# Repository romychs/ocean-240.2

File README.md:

# Компьютер "Океан-240.2"

Схема и печатная плата новодела компьютера "Океан-240.2". Разработана на основе информации из журнала МПСС и на основе схем, чертежей, правок пользователей форума zx-pk.ru (__L Juriy__, __tnt23__, __ivagor__ и других).

## Основные характеристики

|-|-|
|----------------------------------------|------------------------|
|Разрядность, бит                        |                      8 |
|Быстродействие (рег. — рег.), операций/с|                600 000 |
|Емкость ОЗУ, К байт					 |                128/512 |
|Емкость РПЗУ, К байт					 |                     16 |
|__Монитор (серийный цветной):__         |                        |
| в монохромном режиме                   |20 строк по 64 символа  |
| в цветном режиме (4 цвета)             |графическое поле 256x256|
|Клавиатура        | алфавитно-цифровая с контроллером на КМОП ИС |        
|__Интерфейс:__                          |                        |
| последовательный                       | RS232                  | 
| три параллельных программируемых канала| КР580ВВ55              |
| интерфейс печатающего устройства       | ИРПР                   |

__Программное обеспечение:__ монитор с графическими функциями, интерпретатор Бэйсик, квазидисковая операционная система, совместимая с CP/M.

Автор ПЭВМ - __Д. А. Тилинин__

[Исходники](Sources)

[Готовые схемы](Export)

[Прошивки для микросхем ПЗУ](ROMs)

[Файлы для производства печатной платы](Gerbers/Gerber_Ocean-240.2_v1.0.3.zip)

[Темы на форуме zx.pk.ru](https://zx-pk.ru/forums/113-okean-240.html)

## Изменения
- В версии v1.0.1, Дизассемблированы обе микросхемы ПЗУ, на основе информации из полученных исходников, немного скорректирована схема и печатная плата.
- В версии v1.0.2, Микросхемы DD5 и DD22 на схемах и шелке KiCAD, ошибочно отмечены как ЛИ1. Ошибку заметил при сборке *felix*.
- В версии v1.0.3, Исправлены ошибки предыдущей версии. Документация в папке Export и герберы сгенерированы в KiCAD. Версия EasyEDA больше не будет дорабатываться.

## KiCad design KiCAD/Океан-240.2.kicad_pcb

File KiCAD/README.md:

# Океан-240.2 Персональный компьютер

Схема и печатная плата в [KiCAD](https://www.kicad.org/) v9.0

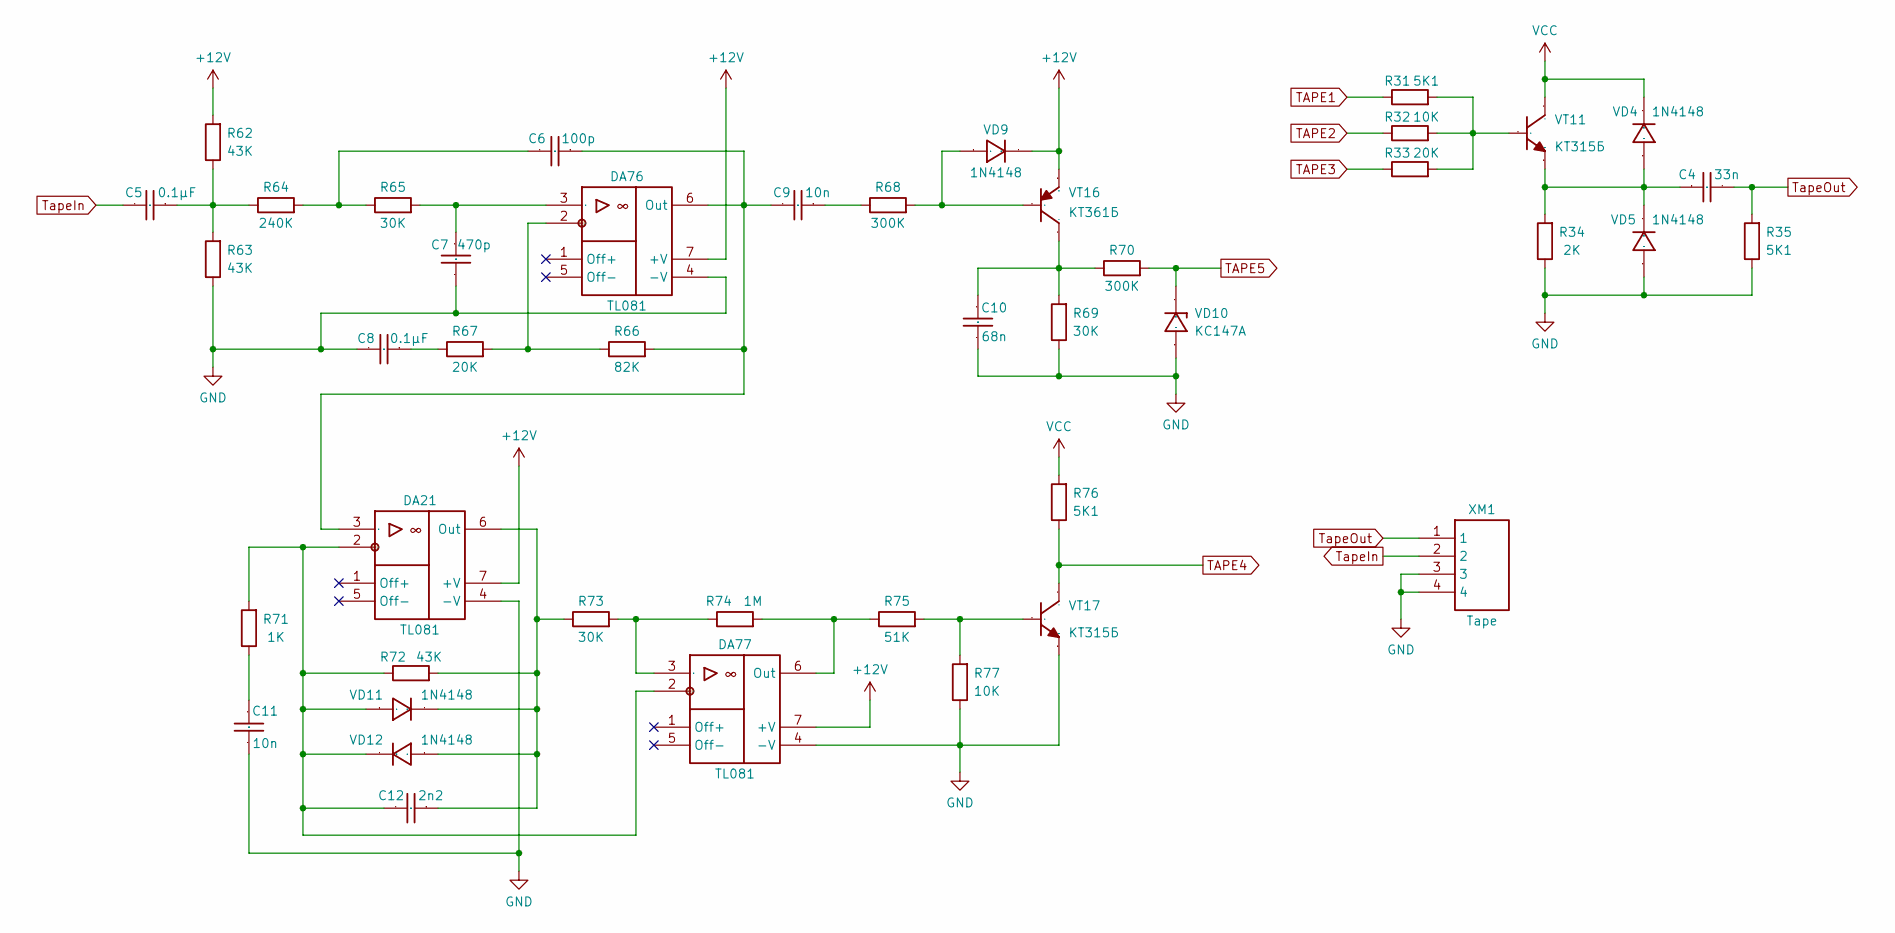
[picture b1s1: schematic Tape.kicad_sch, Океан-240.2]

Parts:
C4: 33n; CAP-TH_L5.08
C5, C8: 0.1μF; CAP-TH_L7.62
C6: 100p; CAP-TH_L7.62
C7: 470p; CAP-TH_L7.62
C9, C11: 10n; CAP-TH_L7.62
C10: 68n; CAP-TH_L7.62
C12: 2n2; CAP-TH_L7.62
DA21, DA76, DA77: TL081; DIP-8_W7.62mm
R31, R35, R76: 5K1; RES_0.125W_P7.62
R32, R77: 10K; RES_0.125W_P7.62
R33, R67: 20K; RES_0.125W_P7.62
R34: 2K; RES_0.125W_P7.62
R62, R63, R72: 43K; RES_0.125W_P7.62
R64: 240K; RES_0.125W_P7.62
R65, R69, R73: 30K; RES_0.125W_P7.62
R66: 82K; RES_0.125W_P7.62
R68, R70: 300K; RES_0.125W_P7.62
R71: 1K; RES_0.125W_P7.62
R74: 1M; RES_0.125W_P7.62
R75: 51K; RES_0.125W_P7.62
VD4, VD5, VD9, VD11, VD12: 1N4148; DO-35_TH_P7.62
VD10: КС147А; DIODE_TH_7.62
VT11, VT17: КТ315Б; KT315_STD
VT16: КТ361Б; KT315_STD
XM1: Tape; HDR-4P-M-P2.54

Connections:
+12V: DA21.7 (+V), DA76.7 (+V), DA77.7 (+V), R62.2, VD9.2 (K), VT16.1 (E); also elsewhere on the board
GND: C7.1, C8.2, C10.1, C11.1, DA21.4 (-V), DA76.4 (-V), DA77.4 (-V), R34.1, R35.1, R63.1, R69.1, R77.1, VD5.1 (A), VD10.1 (A), VT17.1 (E), XM1.3, XM1.4; also elsewhere on the board
unnamed: C5.1, R62.1, R63.2, R64.1
unnamed: C6.2, R64.2, R65.1
unnamed: C8.1, R67.1
unnamed: C9.1, R68.1
unnamed: C11.2, R71.1
unnamed: C6.1, C9.2, DA21.3 (+), DA76.6 (Out), R66.2
unnamed: C12.2, DA21.2 (-), DA77.2 (-), R71.2, R72.1, VD11.1 (A), VD12.2 (K)
unnamed: C12.1, DA21.6 (Out), R72.2, R73.1, VD11.2 (K), VD12.1 (A)
unnamed: C7.2, DA76.3 (+), R65.2
unnamed: DA76.2 (-), R66.1, R67.2
unnamed: DA77.3 (+), R73.2, R74.1
unnamed: DA77.6 (Out), R74.2, R75.1
unnamed: C4.1, R34.2, VD4.1 (A), VD5.2 (K), VT11.1 (E)
unnamed: R68.2, VD9.1 (A), VT16.3 (B)
unnamed: R31.2, R32.2, R33.2, VT11.3 (B)
unnamed: C10.2, R69.2, R70.1, VT16.2 (C)
unnamed: R75.2, R77.2, VT17.3 (B)
TAPE1: R31.1; also elsewhere on the board
TAPE2: R32.1; also elsewhere on the board
TAPE3: R33.1; also elsewhere on the board
TAPE4: R76.1, VT17.2 (C); also elsewhere on the board
TAPE5: R70.2, VD10.2 (K); also elsewhere on the board
TapeIn: C5.2, XM1.2
TapeOut: C4.2, R35.2, XM1.1
VCC: R76.2, VD4.2 (K), VT11.2 (C); also elsewhere on the board

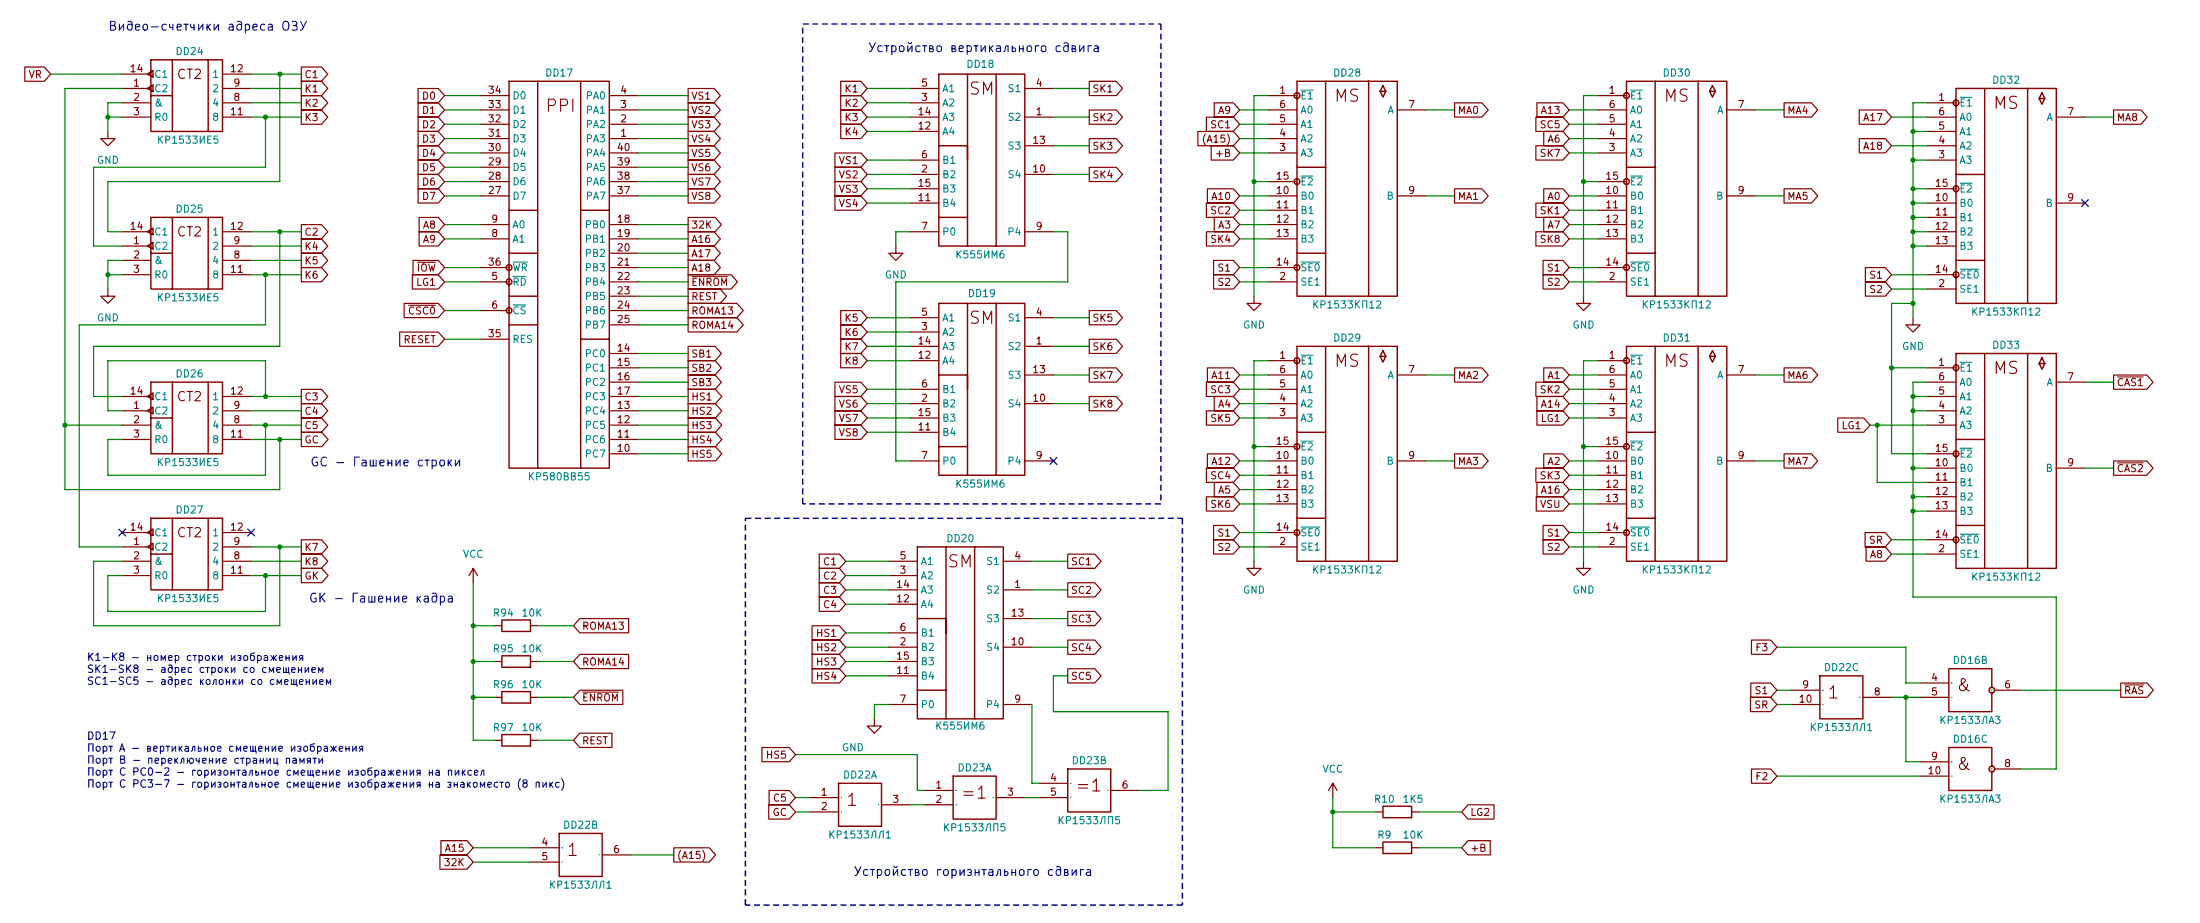
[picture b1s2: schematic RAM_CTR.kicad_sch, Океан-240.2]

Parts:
DD16: КР1533ЛА3; DIP-14_W7.62mm
DD17: КР580ВВ55; DIP-40_W15.24mm_Socket
DD18, DD19, DD20: К555ИМ6; DIP-16_W7.62mm
DD22: КР1533ЛЛ1; DIP-14_W7.62mm
DD23: КР1533ЛП5; DIP-14_W7.62mm
DD24, DD25, DD26, DD27: КР1533ИЕ5; DIP-14_W7.62mm
DD28, DD29, DD30, DD31, DD32, DD33: КР1533КП12; DIP-16_W7.62mm
R9, R94, R95, R96, R97: 10K; RES_0.125W_P7.62
R10: 1K5; RES_0.125W_P7.62

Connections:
32K: DD17.18 (PB0), DD22.5 (2)
(A15): DD22.6 (3), DD28.4 (A2)
+B: DD28.3 (A3), R9.2
A0: DD30.10 (B0); also elsewhere on the board
A1: DD31.6 (A0); also elsewhere on the board
A2: DD31.10 (B0); also elsewhere on the board
A3: DD28.12 (B2); also elsewhere on the board
A4: DD29.4 (A2); also elsewhere on the board
A5: DD29.12 (B2); also elsewhere on the board
A6: DD30.4 (A2); also elsewhere on the board
A7: DD30.12 (B2); also elsewhere on the board
A8: DD17.9 (A0), DD33.2 (SE1); also elsewhere on the board
A9: DD17.8 (A1), DD28.6 (A0); also elsewhere on the board
A10: DD28.10 (B0); also elsewhere on the board
A11: DD29.6 (A0); also elsewhere on the board
A12: DD29.10 (B0); also elsewhere on the board
A13: DD30.6 (A0); also elsewhere on the board
A14: DD31.4 (A2); also elsewhere on the board
A15: DD22.4 (1); also elsewhere on the board
A16: DD17.19 (PB1), DD31.12 (B2)
A17: DD17.20 (PB2), DD32.6 (A0)
A18: DD17.21 (PB3), DD32.4 (A2)
C1: DD20.5 (A1), DD24.12 (1), DD25.14 (C1)
C2: DD20.3 (A2), DD25.12 (1), DD26.14 (C1)
C3: DD20.14 (A3), DD26.1 (C2), DD26.12 (1); also elsewhere on the board
C4: DD20.12 (A4), DD26.9 (2); also elsewhere on the board
C5: DD22.1, DD26.3 (R0), DD26.8 (4)
D0: DD17.34 (D0); also elsewhere on the board
D1: DD17.33 (D1); also elsewhere on the board
D2: DD17.32 (D2); also elsewhere on the board
D3: DD17.31 (D3); also elsewhere on the board
D4: DD17.30 (D4); also elsewhere on the board
D5: DD17.29 (D5); also elsewhere on the board
D6: DD17.28 (D6); also elsewhere on the board
D7: DD17.27 (D7); also elsewhere on the board
F2: DD16.10 (2); also elsewhere on the board
F3: DD16.4 (1); also elsewhere on the board
GC: DD22.2, DD24.1 (C2), DD26.2 (&), DD26.11 (8); also elsewhere on the board
GK: DD27.3 (R0), DD27.11 (8); also elsewhere on the board
GND: DD17.7 (GND), DD18.7 (P0), DD18.8 (GND), DD19.8 (GND), DD20.7 (P0), DD20.8 (GND), DD22.7 (GND), DD23.7 (GND), DD24.2 (&), DD24.3 (R0), DD24.10 (GND), DD25.2 (&), DD25.3 (R0), DD25.10 (GND), DD26.10 (GND), DD27.10 (GND), DD28.1 (~E1), DD28.8 (GND), DD28.15 (~E2), DD29.1 (~E1), DD29.8 (GND), DD29.15 (~E2), DD30.1 (~E1), DD30.8 (GND), DD30.15 (~E2), DD31.1 (~E1), DD31.8 (GND), DD31.15 (~E2), DD32.1 (~E1), DD32.3 (A3), DD32.5 (A1), DD32.8 (GND), DD32.10 (B0), DD32.11 (B1), DD32.12 (B2), DD32.13 (B3), DD32.15 (~E2), DD33.1 (~E1), DD33.8 (GND), DD33.15 (~E2); also elsewhere on the board
HS1: DD17.17 (PC3), DD20.6 (B1)
HS2: DD17.13 (PC4), DD20.2 (B2)
HS3: DD17.12 (PC5), DD20.15 (B3)
HS4: DD17.11 (PC6), DD20.11 (B4)
HS5: DD17.10 (PC7), DD23.1
K1: DD18.5 (A1), DD24.9 (2)
K2: DD18.3 (A2), DD24.8 (4)
K3: DD18.14 (A3), DD24.11 (8), DD25.1 (C2)
K4: DD18.12 (A4), DD25.9 (2)
K5: DD19.5 (A1), DD25.8 (4); also elsewhere on the board
K6: DD19.3 (A2), DD25.11 (8), DD27.1 (C2); also elsewhere on the board
K7: DD19.14 (A3), DD27.2 (&), DD27.9 (2)
K8: DD19.12 (A4), DD27.8 (4)
LG1: DD17.5 (~RD), DD31.3 (A3), DD33.3 (A3), DD33.11 (B1); also elsewhere on the board
LG2: R10.2; also elsewhere on the board
MA0: DD28.7 (A); also elsewhere on the board
MA1: DD28.9 (B); also elsewhere on the board
MA2: DD29.7 (A); also elsewhere on the board
MA3: DD29.9 (B); also elsewhere on the board
MA4: DD30.7 (A); also elsewhere on the board
MA5: DD30.9 (B); also elsewhere on the board
MA6: DD31.7 (A); also elsewhere on the board
MA7: DD31.9 (B); also elsewhere on the board
MA8: DD32.7 (A); also elsewhere on the board
unnamed: DD16.5 (2), DD16.9 (1), DD22.8 (3)
unnamed: DD16.8 (3), DD33.4 (A2), DD33.5 (A1), DD33.6 (A0), DD33.10 (B0), DD33.12 (B2), DD33.13 (B3)
unnamed: DD18.9 (P4), DD19.7 (P0)
unnamed: DD20.9 (P4), DD23.4 (1)
unnamed: DD22.3, DD23.2
unnamed: DD23.3, DD23.5 (2)
RESET: DD17.35 (RES); also elsewhere on the board
REST: DD17.23 (PB5), R97.2; also elsewhere on the board
ROMA13: DD17.24 (PB6), R94.2; also elsewhere on the board
ROMA14: DD17.25 (PB7), R95.2; also elsewhere on the board
S1: DD22.9 (1), DD28.14 (~SE0), DD29.14 (~SE0), DD30.14 (~SE0), DD31.14 (~SE0), DD32.14 (~SE0); also elsewhere on the board
S2: DD28.2 (SE1), DD29.2 (SE1), DD30.2 (SE1), DD31.2 (SE1), DD32.2 (SE1); also elsewhere on the board
SB1: DD17.14 (PC0); also elsewhere on the board
SB2: DD17.15 (PC1); also elsewhere on the board
SB3: DD17.16 (PC2); also elsewhere on the board
SC1: DD20.4 (S1), DD28.5 (A1)
SC2: DD20.1 (S2), DD28.11 (B1)
SC3: DD20.13 (S3), DD29.5 (A1)
SC4: DD20.10 (S4), DD29.11 (B1)
SC5: DD23.6 (3), DD30.5 (A1)
SK1: DD18.4 (S1), DD30.11 (B1)
SK2: DD18.1 (S2), DD31.5 (A1)
SK3: DD18.13 (S3), DD31.11 (B1)
SK4: DD18.10 (S4), DD28.13 (B3)
SK5: DD19.4 (S1), DD29.3 (A3)
SK6: DD19.1 (S2), DD29.13 (B3)
SK7: DD19.13 (S3), DD30.3 (A3)
SK8: DD19.10 (S4), DD30.13 (B3)
SR: DD22.10 (2), DD33.14 (~SE0); also elsewhere on the board
VCC: DD17.26 (VCC), DD18.16 (VCC), DD19.16 (VCC), DD20.16 (VCC), DD22.14 (VCC), DD23.14 (VCC), DD24.5 (VCC), DD25.5 (VCC), DD26.5 (VCC), DD27.5 (VCC), DD28.16 (VCC), DD29.16 (VCC), DD30.16 (VCC), DD31.16 (VCC), DD32.16 (VCC), DD33.16 (VCC), R9.1, R10.1, R94.1, R95.1, R96.1, R97.1; also elsewhere on the board
VR: DD24.14 (C1); also elsewhere on the board
VS1: DD17.4 (PA0), DD18.6 (B1)
VS2: DD17.3 (PA1), DD18.2 (B2)
VS3: DD17.2 (PA2), DD18.15 (B3)
VS4: DD17.1 (PA3), DD18.11 (B4)
VS5: DD17.40 (PA4), DD19.6 (B1)
VS6: DD17.39 (PA5), DD19.2 (B2)
VS7: DD17.38 (PA6), DD19.15 (B3)
VS8: DD17.37 (PA7), DD19.11 (B4)
VSU: DD31.13 (B3); also elsewhere on the board
~CAS1: DD33.7 (A); also elsewhere on the board
~CAS2: DD33.9 (B); also elsewhere on the board
~CSC0: DD17.6 (~CS); also elsewhere on the board
~ENROM: DD17.22 (PB4), R96.2; also elsewhere on the board
~IOW: DD17.36 (~WR); also elsewhere on the board
~RAS: DD16.6 (3); also elsewhere on the board

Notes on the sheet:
Устройство горизнтального сдвига
GK - Гашение кадра
K1-K8 - номер строки изображения SK1-SK8 - адрес строки со смещением SC1-SC5 - адрес колонки со смещением
Видео-счетчики адреса ОЗУ
GC - Гашение строки
Устройство вертикального сдвига
DD17 Порт А - вертикальное смещение изображения Порт B - переключение страниц памяти Порт C PC0-2 - горизонтальное смещение изображения на пиксел Порт C PC3-7 - горизонтальное смещение изображения на знакоместо (8 пикс)

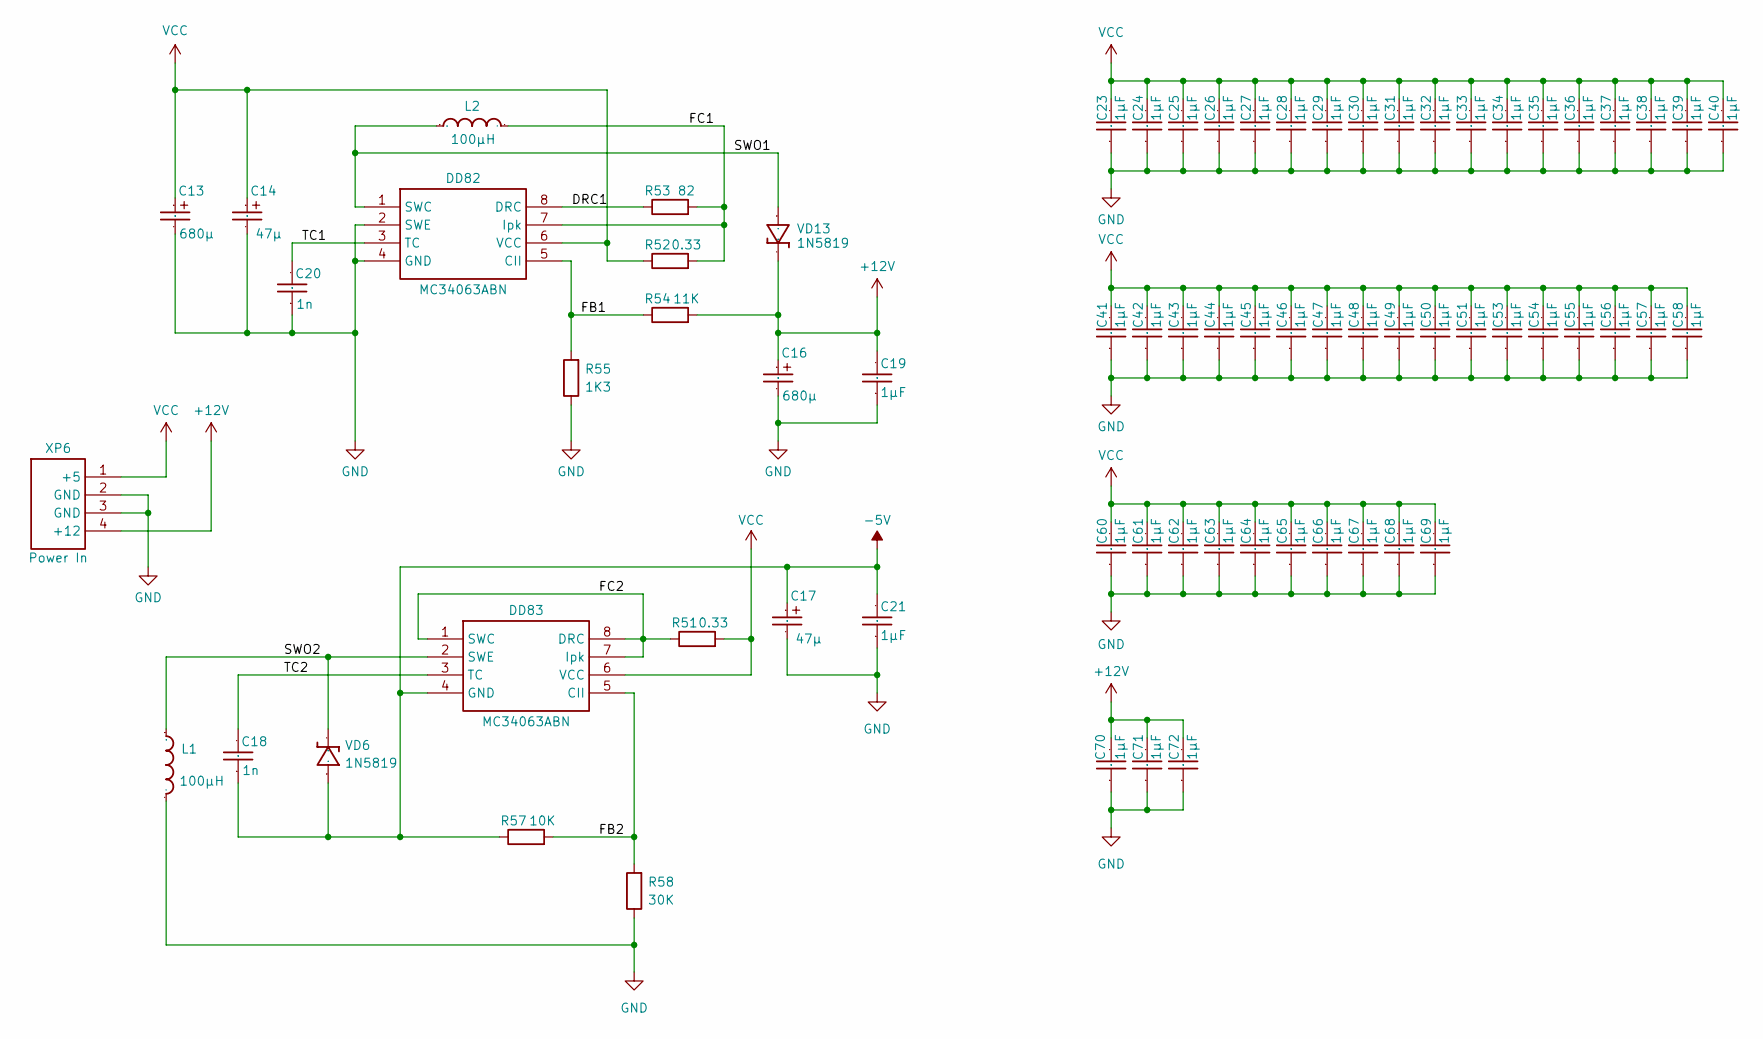
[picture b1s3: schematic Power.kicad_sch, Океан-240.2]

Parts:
C13, C16: 680μ; CAP_P-TH-8x15-P3.556
C14, C17: 47μ; CAP_P-TH-5x11-P2.54
C18: 1n; CAP-TH_L7.62
C19, C23, C24, C25, C26, C27, C28, C29, C30, C31, C32, C33, C34, C35, C36, C37, C38, C39, C40, C41, C42, C43, C44, C45, C46, C47, C48, C49, C50, C51, C53, C54, C55, C56, C57, C58, C60, C61, C62, C63, C64, C65, C66, C67, C68, C69, C70, C71, C72: 1μF; CAP-TH_L7.62
C20: 1n; CAP-TH_L5.08
C21: 1μF; CAP-TH_L5.08
DD82, DD83: MC34063ABN; DIP-8_W7.62mm
L1, L2: 100μH; L_Axial_L7.0mm_D3.3mm_P12.70mm_Horizontal_Fastron_MICC
R51, R52: 0.33; RES_0.125W_P7.62
R53: 82; RES_0.125W_P7.62
R54: 11K; RES_0.125W_P7.62
R55: 1K3; RES_0.125W_P7.62
R57: 10K; RES_0.125W_P7.62
R58: 30K; RES_0.125W_P7.62
VD6, VD13: 1N5819; DO-41_STD_P10.16
XP6: Power In; JVC_MINI-TH-4P

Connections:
+12V: C16.1, C19.2, C70.2, C71.2, C72.2, R54.2, VD13.2 (K), XP6.4 (+12); also elsewhere on the board
-5V: C17.1, C18.1, C21.2, DD83.4 (GND), R57.1, VD6.1 (A); also elsewhere on the board
/Океан-240.2 - Источники питания/DRC1: DD82.8 (DRC), R53.1
/Океан-240.2 - Источники питания/FB1: DD82.5 (CII), R54.1, R55.2
/Океан-240.2 - Источники питания/FB2: DD83.5 (CII), R57.2, R58.2
/Океан-240.2 - Источники питания/FC1: DD82.7 (Ipk), L2.2, R52.2, R53.2
/Океан-240.2 - Источники питания/FC2: DD83.1 (SWC), DD83.7 (Ipk), DD83.8 (DRC), R51.1
/Океан-240.2 - Источники питания/SWO1: DD82.1 (SWC), L2.1, VD13.1 (A)
/Океан-240.2 - Источники питания/SWO2: DD83.2 (SWE), L1.1, VD6.2 (K)
/Океан-240.2 - Источники питания/TC1: C20.2, DD82.3 (TC)
/Океан-240.2 - Источники питания/TC2: C18.2, DD83.3 (TC)
GND: C13.2, C14.2, C16.2, C17.2, C19.1, C20.1, C21.1, C23.1, C24.1, C25.1, C26.1, C27.1, C28.1, C29.1, C30.1, C31.1, C32.1, C33.1, C34.1, C35.1, C36.1, C37.1, C38.1, C39.1, C40.1, C41.1, C42.1, C43.1, C44.1, C45.1, C46.1, C47.1, C48.1, C49.1, C50.1, C51.1, C53.1, C54.1, C55.1, C56.1, C57.1, C58.1, C60.1, C61.1, C62.1, C63.1, C64.1, C65.1, C66.1, C67.1, C68.1, C69.1, C70.1, C71.1, C72.1, DD82.2 (SWE), DD82.4 (GND), L1.2, R55.1, R58.1, XP6.2 (GND), XP6.3 (GND); also elsewhere on the board
VCC: C13.1, C14.1, C23.2, C24.2, C25.2, C26.2, C27.2, C28.2, C29.2, C30.2, C31.2, C32.2, C33.2, C34.2, C35.2, C36.2, C37.2, C38.2, C39.2, C40.2, C41.2, C42.2, C43.2, C44.2, C45.2, C46.2, C47.2, C48.2, C49.2, C50.2, C51.2, C53.2, C54.2, C55.2, C56.2, C57.2, C58.2, C60.2, C61.2, C62.2, C63.2, C64.2, C65.2, C66.2, C67.2, C68.2, C69.2, DD82.6 (VCC), DD83.6 (VCC), R51.2, R52.1, XP6.1 (+5); also elsewhere on the board

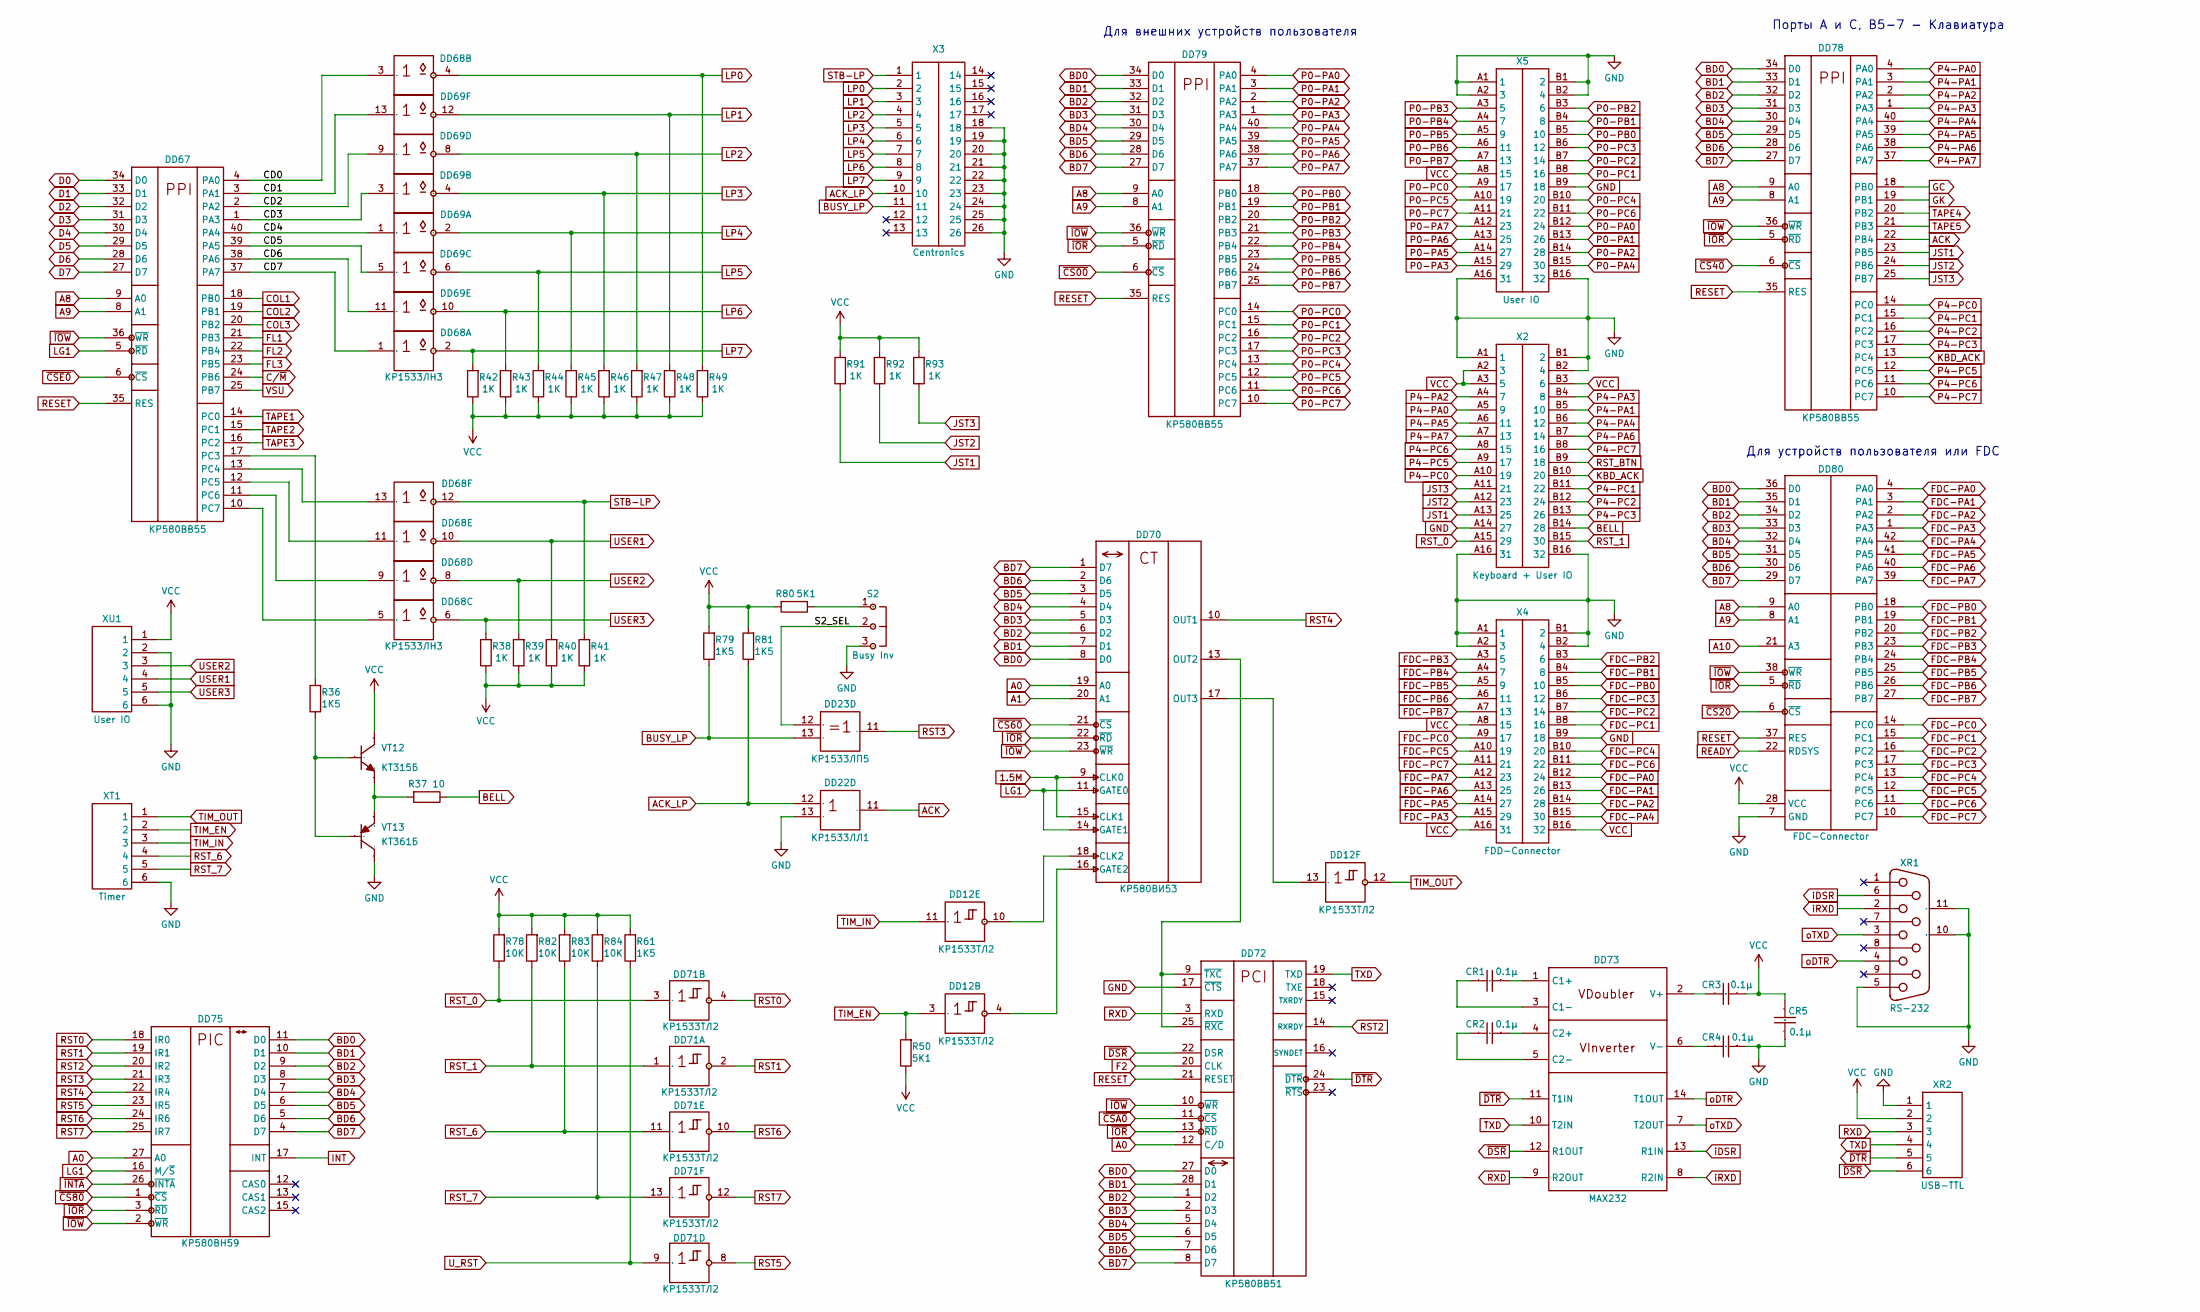
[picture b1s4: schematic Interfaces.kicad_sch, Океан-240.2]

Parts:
CR1, CR2, CR3, CR4, CR5: 0.1μ; CAP-TH_L5.08
DD12, DD71: КР1533ТЛ2; DIP-14_W7.62mm
DD22: КР1533ЛЛ1; DIP-14_W7.62mm
DD23: КР1533ЛП5; DIP-14_W7.62mm
DD67, DD78, DD79: КР580ВВ55; DIP-40_W15.24mm_Socket
DD68, DD69: КР1533ЛН3; DIP-14_W7.62mm
DD70: КР580ВИ53; DIP-24_W15.24mm
DD72: КР580ВВ51; DIP-28_W15.24mm
DD73: MAX232; DIP-16_W7.62mm
DD75: КР580ВН59; DIP-28_W15.24mm
DD80: FDC-Connector; DIP-42_W15.24mm_Socket
R36, R61, R79, R81: 1K5; RES_0.125W_P7.62
R37: 10; RES_0.125W_P7.62
R38, R39, R40, R41, R42, R43, R44, R45, R46, R47, R48, R49, R91, R92, R93: 1K; RES_0.125W_P7.62
R50, R80: 5K1; RES_0.125W_P7.62
R78, R82, R83, R84: 10K; RES_0.125W_P7.62
S2: Busy Inv; HDR-3P-M-P2.54
VT12: КТ315Б; KT315_STD
VT13: КТ361Б; KT315_STD
X2: Keyboard + User IO; DIN_41612_16X2P_F
X3: Centronics; IDC-TH_26P-P2.54M
X4: FDD-Connector; DIN_41612_16X2P_F
X5: User IO; DIN_41612_16X2P_F
XR1: RS-232; DB9-TH
XR2: USB-TTL; HDR-6P-M-P2.54
XT1: Timer; HDR-6P-M-P2.54
XU1: User IO; HDR-6P-M-P2.54

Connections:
1.5M: DD70.9 (CLK0), DD70.15 (CLK1); also elsewhere on the board
/Океан-240.2 - Интерфейсы/CD0: DD67.4 (PA0), DD68.3 (1)
/Океан-240.2 - Интерфейсы/CD1: DD67.3 (PA1), DD69.13 (1)
/Океан-240.2 - Интерфейсы/CD2: DD67.2 (PA2), DD69.9 (1)
/Океан-240.2 - Интерфейсы/CD3: DD67.1 (PA3), DD69.3 (1)
/Океан-240.2 - Интерфейсы/CD4: DD67.40 (PA4), DD69.1
/Океан-240.2 - Интерфейсы/CD5: DD67.39 (PA5), DD69.5 (1)
/Океан-240.2 - Интерфейсы/CD6: DD67.38 (PA6), DD69.11 (1)
/Океан-240.2 - Интерфейсы/CD7: DD67.37 (PA7), DD68.1
/Океан-240.2 - Интерфейсы/S2_SEL: DD23.12 (1), S2.2
A0: DD70.19 (A0), DD72.12 (C/D), DD75.27 (A0); also elsewhere on the board
A1: DD70.20 (A1); also elsewhere on the board
A8: DD67.9 (A0), DD78.9 (A0), DD79.9 (A0), DD80.9 (A0); also elsewhere on the board
A9: DD67.8 (A1), DD78.8 (A1), DD79.8 (A1), DD80.8 (A1); also elsewhere on the board
A10: DD80.21 (A3); also elsewhere on the board
ACK: DD22.11 (3), DD78.22 (PB4)
ACK_LP: DD22.12 (1), R81.1, X3.10
BD0: DD70.8 (D0), DD72.27 (D0), DD75.11 (D0), DD78.34 (D0), DD79.34 (D0), DD80.36 (D0); also elsewhere on the board
BD1: DD70.7 (D1), DD72.28 (D1), DD75.10 (D1), DD78.33 (D1), DD79.33 (D1), DD80.35 (D1); also elsewhere on the board
BD2: DD70.6 (D2), DD72.1 (D2), DD75.9 (D2), DD78.32 (D2), DD79.32 (D2), DD80.34 (D2); also elsewhere on the board
BD3: DD70.5 (D3), DD72.2 (D3), DD75.8 (D3), DD78.31 (D3), DD79.31 (D3), DD80.33 (D3); also elsewhere on the board
BD4: DD70.4 (D4), DD72.5 (D4), DD75.7 (D4), DD78.30 (D4), DD79.30 (D4), DD80.32 (D4); also elsewhere on the board
BD5: DD70.3 (D5), DD72.6 (D5), DD75.6 (D5), DD78.29 (D5), DD79.29 (D5), DD80.31 (D5); also elsewhere on the board
BD6: DD70.2 (D6), DD72.7 (D6), DD75.5 (D6), DD78.28 (D6), DD79.28 (D6), DD80.30 (D6); also elsewhere on the board
BD7: DD70.1 (D7), DD72.8 (D7), DD75.4 (D7), DD78.27 (D7), DD79.27 (D7), DD80.29 (D7); also elsewhere on the board
BELL: R37.1, X2.B14 (28)
BUSY_LP: DD23.13 (2), R79.1, X3.11
COL1: DD67.18 (PB0); also elsewhere on the board
COL2: DD67.19 (PB1); also elsewhere on the board
COL3: DD67.20 (PB2); also elsewhere on the board
C/~M: DD67.24 (PB6); also elsewhere on the board
D0: DD67.34 (D0); also elsewhere on the board
D1: DD67.33 (D1); also elsewhere on the board
D2: DD67.32 (D2); also elsewhere on the board
D3: DD67.31 (D3); also elsewhere on the board
D4: DD67.30 (D4); also elsewhere on the board
D5: DD67.29 (D5); also elsewhere on the board
D6: DD67.28 (D6); also elsewhere on the board
D7: DD67.27 (D7); also elsewhere on the board
F2: DD72.20 (CLK); also elsewhere on the board
FDC-PA0: DD80.4 (PA0), X4.B12 (24)
FDC-PA1: DD80.3 (PA1), X4.B13 (26)
FDC-PA2: DD80.2 (PA2), X4.B14 (28)
FDC-PA3: DD80.1 (PA3), X4.A15 (29)
FDC-PA4: DD80.42 (PA4), X4.B15 (30)
FDC-PA5: DD80.41 (PA5), X4.A14 (27)
FDC-PA6: DD80.40 (PA6), X4.A13 (25)
FDC-PA7: DD80.39 (PA7), X4.A12 (23)
FDC-PB0: DD80.18 (PB0), X4.B5 (10)
FDC-PB1: DD80.19 (PB1), X4.B4 (8)
FDC-PB2: DD80.20 (PB2), X4.B3 (6)
FDC-PB3: DD80.23 (PB3), X4.A3 (5)
FDC-PB4: DD80.24 (PB4), X4.A4 (7)
FDC-PB5: DD80.25 (PB5), X4.A5 (9)
FDC-PB6: DD80.26 (PB6), X4.A6 (11)
FDC-PB7: DD80.27 (PB7), X4.A7 (13)
FDC-PC0: DD80.14 (PC0), X4.A9 (17)
FDC-PC1: DD80.15 (PC1), X4.B8 (16)
FDC-PC2: DD80.16 (PC2), X4.B7 (14)
FDC-PC3: DD80.17 (PC3), X4.B6 (12)
FDC-PC4: DD80.13 (PC4), X4.B10 (20)
FDC-PC5: DD80.12 (PC5), X4.A10 (19)
FDC-PC6: DD80.11 (PC6), X4.B11 (22)
FDC-PC7: DD80.10 (PC7), X4.A11 (21)
FL1: DD67.21 (PB3); also elsewhere on the board
FL2: DD67.22 (PB4); also elsewhere on the board
FL3: DD67.23 (PB5); also elsewhere on the board
GC: DD78.18 (PB0); also elsewhere on the board
GK: DD78.19 (PB1); also elsewhere on the board
GND: CR4.1, CR5.2, DD22.13 (2), DD67.7 (GND), DD68.7 (GND), DD69.7 (GND), DD70.12 (GND), DD71.7 (GND), DD72.4 (GND), DD72.17 (~CTS), DD73.15 (GND), DD75.14 (GND), DD78.7 (GND), DD79.7 (GND), DD80.7 (GND), S2.3, VT13.2 (C), X2.A1 (1), X2.A14 (27), X2.A16 (31), X2.B1 (2), X2.B2 (4), X2.B16 (32), X3.18, X3.19, X3.20, X3.21, X3.22, X3.23, X3.24, X3.25, X3.26, X4.A1 (1), X4.A2 (3), X4.B1 (2), X4.B2 (4), X4.B9 (18), X5.A1 (1), X5.A2 (3), X5.A16 (31), X5.B1 (2), X5.B2 (4), X5.B9 (18), X5.B16 (32), XR1.5, XR1.10 (MH1), XR1.11 (MH2), XR2.1, XT1.6, XU1.2, XU1.6; also elsewhere on the board
INT: DD75.17 (INT); also elsewhere on the board
JST1: DD78.23 (PB5), R91.1, X2.A13 (25)
JST2: DD78.24 (PB6), R92.1, X2.A12 (23)
JST3: DD78.25 (PB7), R93.1, X2.A11 (21)
KBD_ACK: DD78.13 (PC4), X2.B10 (20)
LG1: DD67.5 (~RD), DD70.11 (GATE0), DD70.14 (GATE1), DD75.16 (M/~S); also elsewhere on the board
LP0: DD68.4 (2), R49.2, X3.2
LP1: DD69.12 (2), R48.2, X3.3
LP2: DD69.8 (2), R47.2, X3.4
LP3: DD69.4 (2), R46.2, X3.5
LP4: DD69.2, R45.2, X3.6
LP5: DD69.6 (2), R44.2, X3.7
LP6: DD69.10 (2), R43.2, X3.8
LP7: DD68.2, R42.2, X3.9
unnamed: DD12.4 (2), DD70.16 (GATE2)
unnamed: DD12.10 (2), DD70.18 (CLK2)
unnamed: DD12.13 (1), DD70.17 (OUT3)
unnamed: DD67.17 (PC3), R36.2
unnamed: DD67.13 (PC4), DD68.13 (1)
unnamed: DD67.12 (PC5), DD68.11 (1)
unnamed: DD67.11 (PC6), DD68.9 (1)
unnamed: DD67.10 (PC7), DD68.5 (1)
unnamed: DD70.13 (OUT2), DD72.9 (~TXC), DD72.25 (~RXC)
unnamed: CR1.1, DD73.1 (C1+)
unnamed: CR1.2, DD73.3 (C1-)
unnamed: CR2.1, DD73.4 (C2+)
unnamed: CR2.2, DD73.5 (C2-)
unnamed: CR3.2, DD73.2 (V+)
unnamed: CR4.2, DD73.6 (V-)
unnamed: R80.1, S2.1
unnamed: R36.1, VT12.3 (B), VT13.3 (B)
unnamed: R37.2, VT12.1 (E), VT13.1 (E)
P0-PA0: DD79.4 (PA0), X5.B12 (24)
P0-PA1: DD79.3 (PA1), X5.B13 (26)
P0-PA2: DD79.2 (PA2), X5.B14 (28)
P0-PA3: DD79.1 (PA3), X5.A15 (29)
P0-PA4: DD79.40 (PA4), X5.B15 (30)
P0-PA5: DD79.39 (PA5), X5.A14 (27)
P0-PA6: DD79.38 (PA6), X5.A13 (25)
P0-PA7: DD79.37 (PA7), X5.A12 (23)
P0-PB0: DD79.18 (PB0), X5.B5 (10)
P0-PB1: DD79.19 (PB1), X5.B4 (8)
P0-PB2: DD79.20 (PB2), X5.B3 (6)
P0-PB3: DD79.21 (PB3), X5.A3 (5)
P0-PB4: DD79.22 (PB4), X5.A4 (7)
P0-PB5: DD79.23 (PB5), X5.A5 (9)
P0-PB6: DD79.24 (PB6), X5.A6 (11)
P0-PB7: DD79.25 (PB7), X5.A7 (13)
P0-PC0: DD79.14 (PC0), X5.A9 (17)
P0-PC1: DD79.15 (PC1), X5.B8 (16)
P0-PC2: DD79.16 (PC2), X5.B7 (14)
P0-PC3: DD79.17 (PC3), X5.B6 (12)
P0-PC4: DD79.13 (PC4), X5.B10 (20)
P0-PC5: DD79.12 (PC5), X5.A10 (19)
P0-PC6: DD79.11 (PC6), X5.B11 (22)
P0-PC7: DD79.10 (PC7), X5.A11 (21)
P4-PA0: DD78.4 (PA0), X2.A5 (9)
P4-PA1: DD78.3 (PA1), X2.B5 (10)
P4-PA2: DD78.2 (PA2), X2.A4 (7)
P4-PA3: DD78.1 (PA3), X2.B4 (8)
P4-PA4: DD78.40 (PA4), X2.B6 (12)
P4-PA5: DD78.39 (PA5), X2.A6 (11)
P4-PA6: DD78.38 (PA6), X2.B7 (14)
P4-PA7: DD78.37 (PA7), X2.A7 (13)
P4-PC0: DD78.14 (PC0), X2.A10 (19)
P4-PC1: DD78.15 (PC1), X2.B11 (22)
P4-PC2: DD78.16 (PC2), X2.B12 (24)
P4-PC3: DD78.17 (PC3), X2.B13 (26)
P4-PC5: DD78.12 (PC5), X2.A9 (17)
P4-PC6: DD78.11 (PC6), X2.A8 (15)
P4-PC7: DD78.10 (PC7), X2.B8 (16)
READY: DD80.22 (RDSYS); also elsewhere on the board
RESET: DD67.35 (RES), DD72.21 (RESET), DD78.35 (RES), DD79.35 (RES), DD80.37 (RES); also elsewhere on the board
RST0: DD71.4 (2), DD75.18 (IR0)
RST1: DD71.2, DD75.19 (IR1)
RST2: DD72.14 (RXRDY), DD75.20 (IR2)
RST3: DD23.11 (3), DD75.21 (IR3)
RST4: DD70.10 (OUT1), DD75.22 (IR4)
RST5: DD71.8 (2), DD75.23 (IR5)
RST6: DD71.10 (2), DD75.24 (IR6)
RST7: DD71.12 (2), DD75.25 (IR7)
RST_0: DD71.3 (1), R78.1, X2.A15 (29)
RST_1: DD71.1, R82.1, X2.B15 (30)
RST_6: DD71.11 (1), R83.1, XT1.4
RST_7: DD71.13 (1), R84.1, XT1.5
RST_BTN: X2.B9 (18); also elsewhere on the board
RXD: DD72.3 (RXD), DD73.9 (R2OUT), XR2.3
STB-LP: DD68.12 (2), R41.2, X3.1
TAPE1: DD67.14 (PC0); also elsewhere on the board
TAPE2: DD67.15 (PC1); also elsewhere on the board
TAPE3: DD67.16 (PC2); also elsewhere on the board
TAPE4: DD78.20 (PB2); also elsewhere on the board
TAPE5: DD78.21 (PB3); also elsewhere on the board
TIM_EN: DD12.3 (1), R50.2, XT1.2
TIM_IN: DD12.11 (1), XT1.3
TIM_OUT: DD12.12 (2), XT1.1
TXD: DD72.19 (TXD), DD73.10 (T2IN), XR2.4
USER1: DD68.10 (2), R40.2, XU1.4
USER2: DD68.8 (2), R39.2, XU1.3
USER3: DD68.6 (2), R38.2, XU1.5
U_RST: DD71.9 (1), R61.1
VCC: CR3.1, CR5.1, DD67.26 (VCC), DD68.14 (VCC), DD69.14 (VCC), DD70.24 (VCC), DD71.14 (VCC), DD72.26 (VCC), DD73.16 (VCC), DD75.28 (VCC), DD78.26 (VCC), DD79.26 (VCC), DD80.28 (VCC), R38.1, R39.1, R40.1, R41.1, R42.1, R43.1, R44.1, R45.1, R46.1, R47.1, R48.1, R49.1, R50.1, R61.2, R78.2, R79.2, R80.2, R81.2, R82.2, R83.2, R84.2, R91.2, R92.2, R93.2, VT12.2 (C), X2.A2 (3), X2.A3 (5), X2.B3 (6), X4.A8 (15), X4.A16 (31), X4.B16 (32), X5.A8 (15), XR2.2, XU1.1; also elsewhere on the board
VSU: DD67.25 (PB7); also elsewhere on the board
iDSR: DD73.13 (R1IN), XR1.6
iRXD: DD73.8 (R2IN), XR1.2
oDTR: DD73.14 (T1OUT), XR1.4
oTXD: DD73.7 (T2OUT), XR1.3
~CS00: DD79.6 (~CS); also elsewhere on the board
~CS20: DD80.6 (~CS); also elsewhere on the board
~CS40: DD78.6 (~CS); also elsewhere on the board
~CS60: DD70.21 (~CS); also elsewhere on the board
~CS80: DD75.1 (~CS); also elsewhere on the board
~CSA0: DD72.11 (~CS); also elsewhere on the board
~CSE0: DD67.6 (~CS); also elsewhere on the board
~DSR: DD72.22 (DSR), DD73.12 (R1OUT), XR2.6
~DTR: DD72.24 (~DTR), DD73.11 (T1IN), XR2.5
~INTA: DD75.26 (~INTA); also elsewhere on the board
~IOR: DD70.22 (~RD), DD72.13 (~RD), DD75.3 (~RD), DD78.5 (~RD), DD79.5 (~RD), DD80.5 (~RD); also elsewhere on the board
~IOW: DD67.36 (~WR), DD70.23 (~WR), DD72.10 (~WR), DD75.2 (~WR), DD78.36 (~WR), DD79.36 (~WR), DD80.38 (~WR); also elsewhere on the board

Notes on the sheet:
Для внешних устройств пользователя
Порты A и С, B5-7 - Клавиатура
Для устройств пользователя или FDC
